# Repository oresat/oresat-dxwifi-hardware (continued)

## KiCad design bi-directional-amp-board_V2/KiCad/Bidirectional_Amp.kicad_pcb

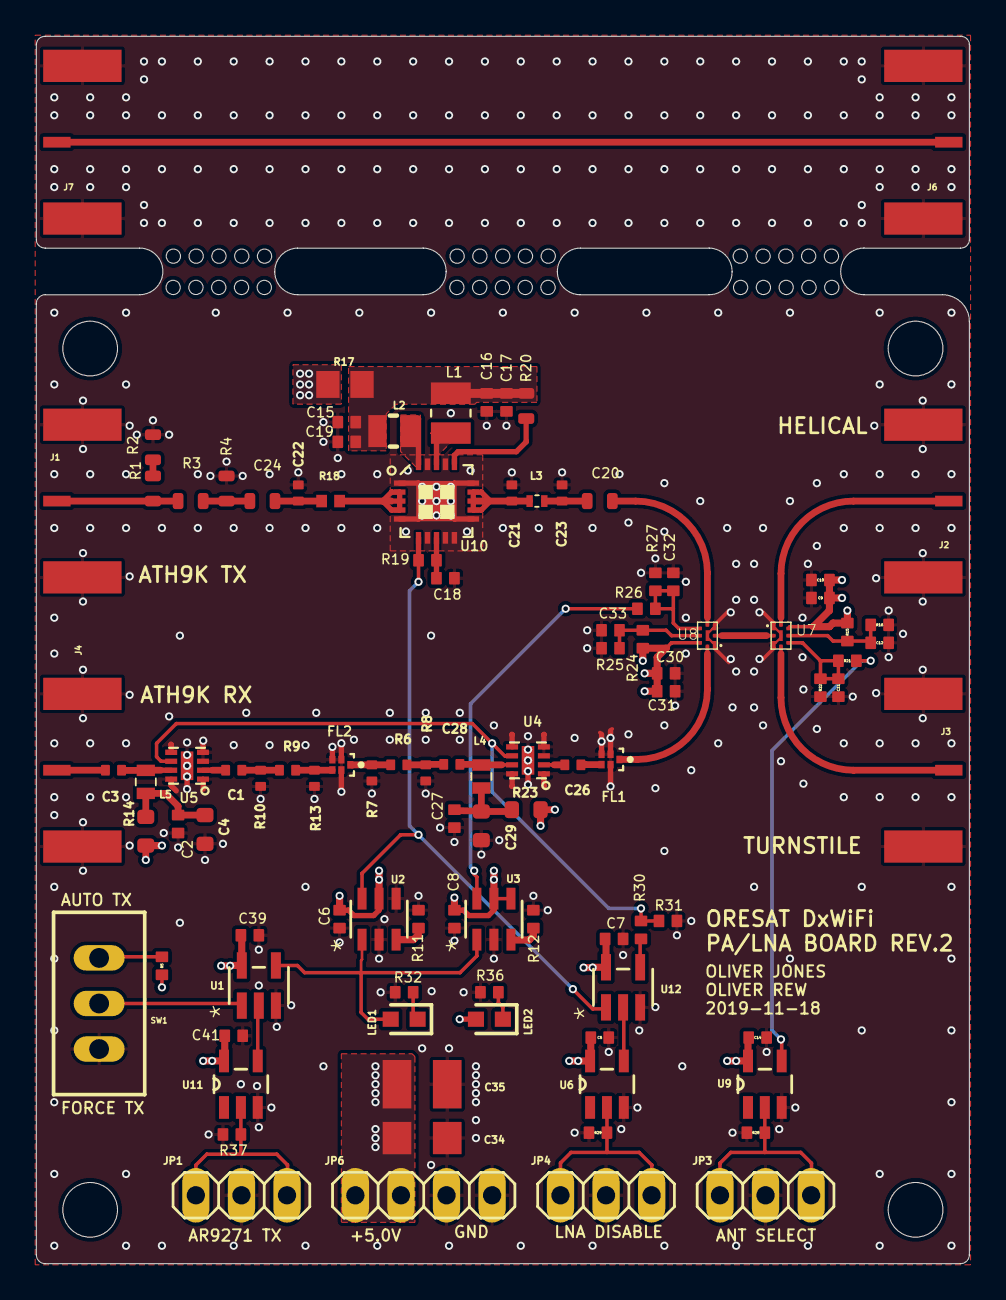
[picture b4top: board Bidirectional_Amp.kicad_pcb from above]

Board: 4 copper layers, 52.0 x 68.4 mm, 135 parts (0 on the bottom side), 53 nets.

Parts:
@HOLE0, @HOLE1, @HOLE2, @HOLE3, @HOLE4, @HOLE5, @HOLE6, @HOLE7, @HOLE8, @HOLE9, @HOLE10, @HOLE11, @HOLE12, @HOLE13, @HOLE14, @HOLE15, @HOLE16, @HOLE17, @HOLE18, @HOLE19, @HOLE20, @HOLE21, @HOLE22, @HOLE23, @HOLE24, @HOLE25, @HOLE26, @HOLE27, @HOLE28, @HOLE29: (no value)
C1, C3, C26, C28: 15p; .0402-C-NOSILK
C2, C27: 15p; .0402-B-NOSILK
C4, C29: 1uF; .0603-B-NOSILK
C5, C6, C7, C8, C10, C14, C31, C39, C41: 100n; .0402-B-NOSILK
C9, C12, C30, C33: 100p; .0402-B-NOSILK
C11, C32: DNP; .0402-B-NOSILK
C15, C16, C17: 100nF; .0402-B-NOSILK
C18: 100pF; .0402-B-NOSILK
C19: 1000pF; .0402-B-NOSILK
C20: 100pF; .0603-C-NOSILK
C21: 3.0pF; .0402-C-NOSILK
C22: 2.2pF; .0402-C-NOSILK
C23: 1.6pF; .0402-C-NOSILK
C24: 4.7pF; .0603-C-NOSILK
C34: 4.7uF; C1206_334
C35: 22uF; C1210_334
FL1, FL2: QPQ1907; FIL_B39162B9417K610
H1, H2, H3, H4: STAND-OFFTIGHT; STAND-OFF-TIGHT
J1, J2, J3, J4, J6, J7: 142-0701-851_ALT; 142-0701-851
JP1, JP3, JP4: 1X03_325
JP6: 1X04_325
L1: 1008HQ-10NXJLB1008_IMPERIAL_2520_METRIC; INDC2520X120N
L2: 6.8nH; 0805CS
L3: 1.2nH; 0402CS1N2XJLW
L4, L5: 68nH; 0603CS-68NXJLW
LED1: LTST-C193KRKT-5A; LEDC1607X80N
LED2: LTST-C193KGKT-5A; LEDC1607X80N
R1, R2: 147; .0603-C-NOSILK
R3: 17.8; .0603-C-NOSILK
R4: 294; .0603-C-NOSILK
R5, R15, R21, R24, R26, R28, R29, R31, R37: 10k; .0402-B-NOSILK
R6, R9: 17.8; .0402-C-NOSILK
R7, R8, R10, R13: 294; .0402-C-NOSILK
R11, R12: 499k; .0402-B-NOSILK
R14, R23: 0; .0603-B-NOSILK
R16, R22, R25, R27: 5.62k; .0402-B-NOSILK
R17: 0; R0805_334
R18: 1.2; R0402_334
R19: 110; .0402-B-NOSILK
R20: 220; .0603-C-NOSILK
R30: 33k; .0402-B-NOSILK
R32, R36: 1k; .0402-B-NOSILK
SW1: TL36PO; TL3XPO_380
U1, U12: SN74LVC1G32DBVR; DBV5
U2, U3: LTC6994-1; TSOT-23_S6
U4, U5: TQP3M9037; DFN8-2X2-WITH-PAD
U6, U9, U11: SN74LV1T34DBVR; SOT95P280X145-5N
U7, U8: QPC1022
U10: TQP9111; QFN50P400X400X102-21N

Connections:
+5V: C5.1, C6.1, C7.1, C8.1, C9.1, C10.1, C14.1, C30.1, C31.1, C34.1, C35.1, C39.1, C41.1, JP6.1, JP6.2, LED2.2, R5.2, R14.2, R15.1, R17.2, R23.2, R24.1, U1.5, U2.5, U3.4, U3.5, U6.5, U7.7, U8.7, U9.5, U11.5, U12.5
ANT_SEL+3.3V: JP3.1, JP3.3, R28.2, U9.2
ANT_SEL_+5.0V: R21.1, U9.4
AR9271_TX_+3.3V: JP1.1, JP1.3, R37.2, U11.2
AS-CTRL: C11.1, R21.2, R22.1, U7.5
AS-EN: C12.1, R15.2, R16.1, U7.6
GND: C2.1, C4.2, C5.2, C6.2, C7.2, C8.2, C9.2, C10.2, C11.2, C12.2, C14.2, C15.2, C16.2, C17.2, C18.2, C19.2, C21.2, C22.2, C23.2, C27.1, C29.2, C30.2, C31.2, C32.2, C33.2, C34.2, C35.2, C39.2, C41.2, FL1.2, FL1.3, FL1.5, FL2.2, FL2.3, FL2.5, J1.GND1, J1.GND2, J1.GND3, J1.GND4, J2.GND1, J2.GND2, J2.GND3, J2.GND4, J3.GND1, J3.GND2, J3.GND3, J3.GND4, J4.GND1, J4.GND2, J4.GND3, J4.GND4, J6.GND1, J6.GND2, J6.GND3, J6.GND4, J7.GND1, J7.GND2, J7.GND3, J7.GND4, JP1.2, JP3.2, JP4.2, JP6.3, JP6.4, R2.1, R4.2, R7.2, R8.2, R10.2, R11.1, R12.1, R13.2, R16.2, R22.2, R25.2, R27.2, R28.1, R29.1, R31.2, R32.1, R36.1, R37.1, SW1.1, U1.3, U2.2, U2.4, U3.2, U4.1, U4.3, U4.4, U4.5, U4.8, U4.PAD, U5.1, U5.3, U5.4, U5.5, U5.8, U5.PAD, U6.3, U7.1, U7.3, U7.9, U8.1, U8.3, U8.9, U9.3, U10.1, U10.5, U10.7, U10.9, U10.10, U10.11, U10.15, U10.17, U10.19, U10.21, U11.3, U12.3
HELICAL: J2.RF1, U7.8
LNA_DISABLE+3.3V: JP4.1, JP4.3, R29.2, U6.2
LNA_DISABLE_+5.0V: U6.4, U12.2
LNA_ON_OFF: R30.1, R31.1, U4.6, U5.6
unnamed: C28.2, R6.1, R8.1
unnamed: J1.RF1, R1.2, R3.1
unnamed: R5.1, SW1.3
unnamed: R1.1, R2.2
unnamed: SW1.2, U1.1
unnamed: FL2.4, R9.1, R13.1
unnamed: C1.2, U5.2
unnamed: C3.1, L5.1, U5.7
unnamed: C2.2, C4.1, L5.2, R14.1
unnamed: LED1.2, U1.4, U2.1, U3.1
unnamed: R11.2, U2.3
unnamed: C3.2, J4.RF1
unnamed: U1.2, U11.4
unnamed: R12.2, U3.3
unnamed: LED1.1, R32.2
unnamed: L1.1, U10.18
unnamed: R30.2, U12.4
unnamed: C15.1, C16.1, C17.1, C19.1, L1.2, L2.2, R17.1, R20.2
unnamed: C18.1, R19.2, U10.8
unnamed: C21.1, L3.1, U10.12, U10.13, U10.14
unnamed: C22.1, C24.2, R18.1
unnamed: C26.2, U4.2
unnamed: C20.1, C23.1, L3.2
unnamed: C28.1, L4.1, U4.7
unnamed: C27.2, C29.1, L4.2, R23.1
unnamed: R20.1, U10.16
unnamed: L2.1, U10.20
unnamed: C26.1, FL1.4
unnamed: LED2.1, R36.2
unnamed: R18.2, U10.2, U10.3, U10.4
PA_MATCH_OUT: C20.2, U8.4
PA_ON_LNA_OFF: R19.1, U2.6, U10.6, U12.1
PA_PAD_OUT: C24.1, R3.2, R4.1
PA_PAD_OUT1: FL2.1, R6.2, R7.1
PA_PAD_OUT2: C1.1, R9.2, R10.1
RX_IN: FL1.1, U8.8
THROUGH: J6.RF1, J7.RF1
TURNSTILE: J3.RF1, U7.4
TXRX-CTRL: C32.1, R26.2, R27.1, U8.5
TXRX-EN: C33.1, R24.2, R25.1, U8.6
TX_RX_COMMON: U7.2, U8.2
TX_RX_CTL: R26.1, U3.6

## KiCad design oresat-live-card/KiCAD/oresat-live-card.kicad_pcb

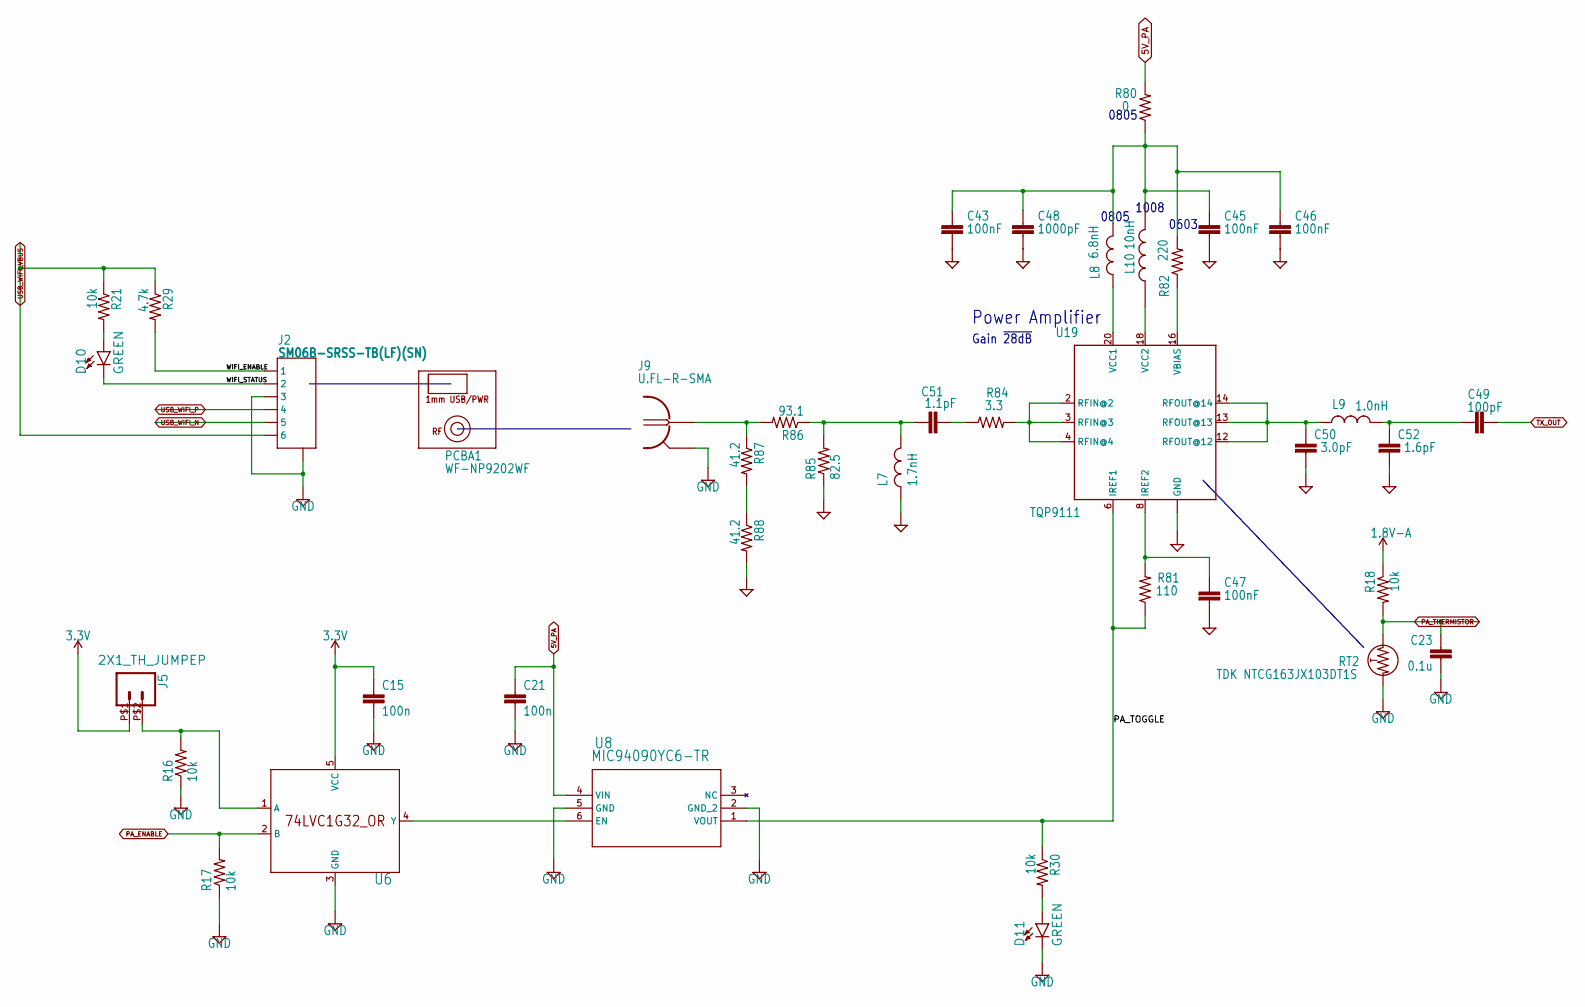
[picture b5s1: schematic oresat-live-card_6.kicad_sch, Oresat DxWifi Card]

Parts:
C15, C21: 100n; .0603-A
C23: 0.1u; .0603-A
C43, C45, C46: CGA2B1X7R1C104K050BC; .0402-B-NOSILK
C47: CGA2B1X7R1C104K050BC; .0402-C-NOSILK
C48: CGA2B2NP01H102J050BA; .0402-B-NOSILK
C49: GCM1885C1H101JA16D; .0402-C-NOSILK
C50: 04025U3R0BAT2A; .0402-C-NOSILK
C51: 04025J1R1PBSTR\500; .0402-C-NOSILK
C52: 04025U1R6BAT2A; .0402-C-NOSILK
D10, D11: 150060VS55040; LED-0603
J2: SM06B-SRSS-TB(LF)(SN); CONN_SM06B-SRSS-TB_JST
J5: 2X1_TH_JUMPEP; 2X1
J9: U.FL-R-SMA; U.FL-R-SMT
L7: 0402DC-1N7XJRU; .0402-C-NOSILK
L8: 0805CS-060XJLC; .0805-C-NOSILK
L9: MLK1005S1N0ST000; .0402-C-NOSILK
L10: Fixed Inductors 1008 10nH Unshld 5% 1.6A 60mOhms; INDC2928X203N
PCBA1: WF-NP9202WF; WF-NP9202
R16, R17, R18, R21, R30: 10k; .0603-A
R29: 4.7k; .0603-A
R80: ERJ-6GEY0R00V; R0805
R81: ERJ-2RKF1100X; .0402-B-NOSILK
R82: ERJ-3EKF2200V; .0603-C-NOSILK
R84: CRCW04023R30FKED; .0402-C-NOSILK
R85: ERJ-3EKF82R5V; .0603-A
R86: ERJ-3EKF93R1V; .0603-A
R87, R88: ERJ-3EKF41R2V; .0603-A
RT2: TDK NTCG163JX103DT1S; 0603-THERMISTOR-B
U6: SN74LVC1G32QDBVRQ1; DBV5
U8: MIC94090YC6-TR; SC-70-6_MCH
U19: TQP9111; QFN50P400X400X102-21N

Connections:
1.8V-A: R18.1; also elsewhere on the board
3.3V: C15.1, J5.P$1 (1), U6.5 (VCC); also elsewhere on the board
5V_PA: C21.1, R80.2, U8.4 (VIN); also elsewhere on the board
/oresat-live-card_6/PA_TOGGLE: R30.1, R81.1, U8.1 (VOUT), U19.6 (IREF1)
/oresat-live-card_6/WIFI_ENABLE: J2.1, R29.2
/oresat-live-card_6/WIFI_STATUS: D10.C, J2.2
unnamed: C43.1, C45.1, C46.1, C48.1, L8.2, L10.2, R80.1, R82.2
unnamed: C47.1, R81.2, U19.8 (IREF2)
unnamed: C49.1, C52.1, L9.2
unnamed: C50.1, L9.1, U19.12 (RFOUT@12), U19.13 (RFOUT@13), U19.14 (RFOUT@14)
unnamed: C51.1, L7.2, R85.2, R86.1
unnamed: C51.2, R84.1
unnamed: D10.A, R21.2
unnamed: D11.A, R30.2
unnamed: J5.P$2 (2), R16.2, U6.1 (A)
unnamed: J9.1, R86.2, R87.1
unnamed: L8.1, U19.20 (VCC1)
unnamed: L10.1, U19.18 (VCC2)
unnamed: R82.1, U19.16 (VBIAS)
unnamed: R84.2, U19.2 (RFIN@2), U19.3 (RFIN@3), U19.4 (RFIN@4)
unnamed: R87.2, R88.1
unnamed: U6.4 (Y), U8.6 (EN)
PA_ENABLE: R17.2, U6.2 (B); also elsewhere on the board
PA_THERMISTOR: C23.1, R18.2, RT2.1; also elsewhere on the board
TX_OUT: C49.2; also elsewhere on the board
USB_WIFI_N: J2.5; also elsewhere on the board
USB_WIFI_P: J2.4; also elsewhere on the board
USB_WIFI_VBUS: J2.6, R21.1, R29.1; also elsewhere on the board

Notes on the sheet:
1008
0805
Gain ~{28dB}
0603
Power Amplifier

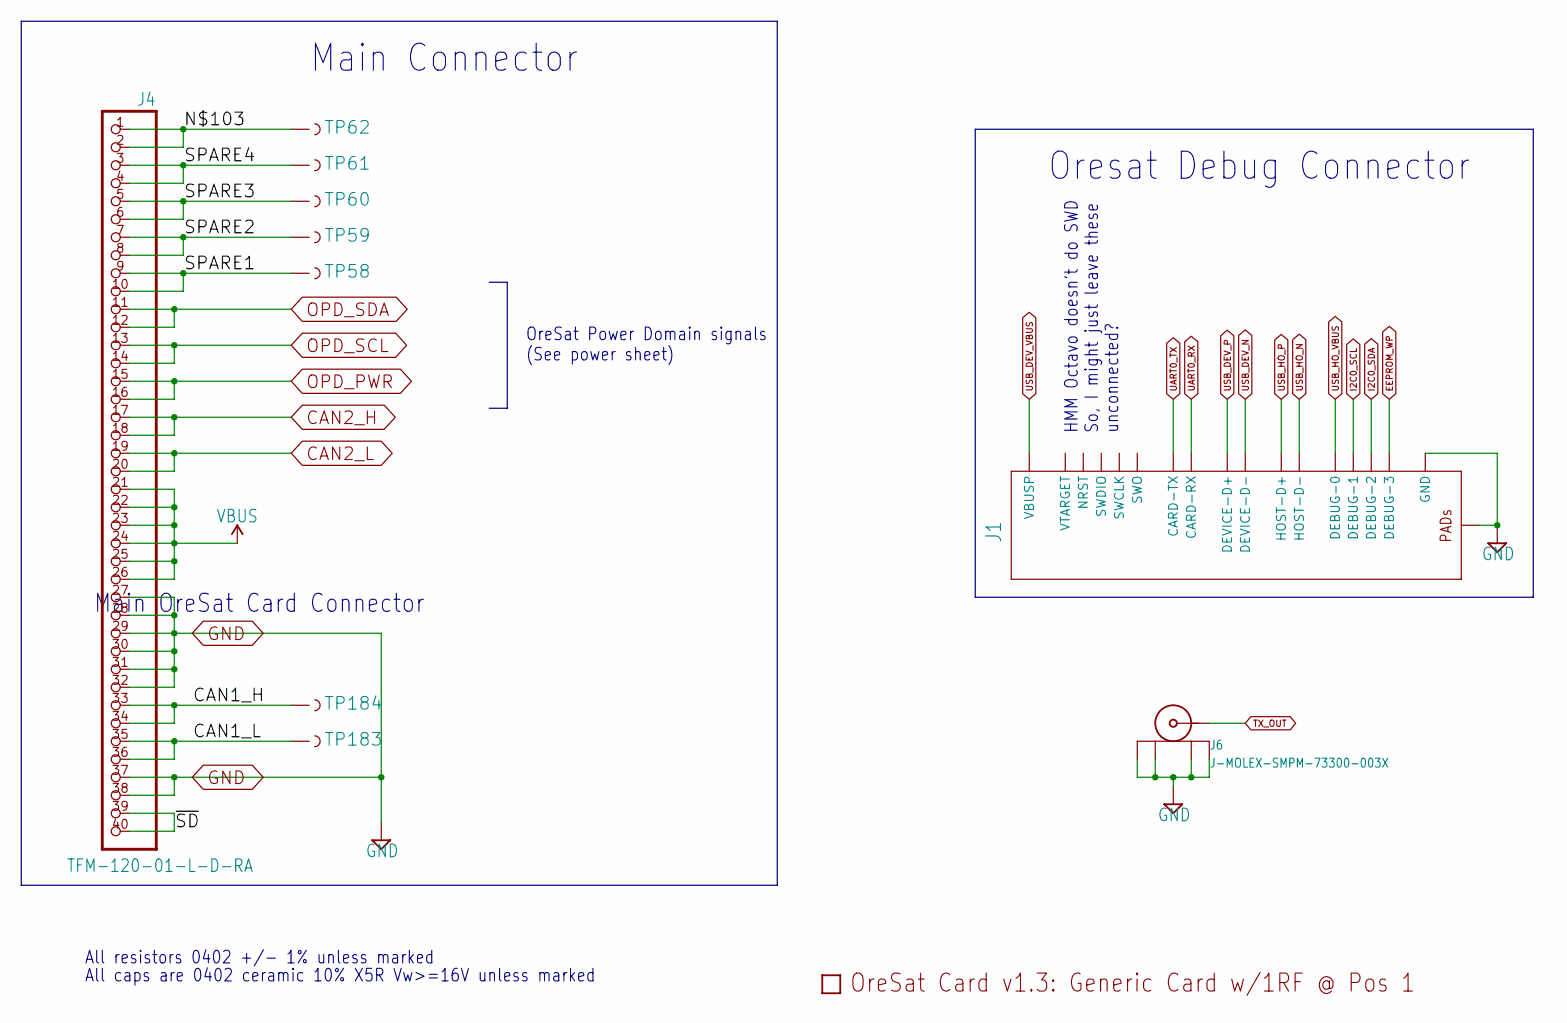
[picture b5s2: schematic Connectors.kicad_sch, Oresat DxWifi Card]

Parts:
J1: ORESAT-DEBUG-CONNECTOR-CARD; TE_2-1734592-0
J4: TFM-120-01-L-D-RA; J-SAMTEC-TFM-120-X1-XXX-D-RA
J6: J-MOLEX-SMPM-73300-003X; J-MOLEX-SMPM-073300-003X
PCB1: ORESAT-CARD-V1.3-GENERIC-1RF-POS1
TP58, TP59, TP60, TP61, TP62, TP183, TP184: TEST-POINT3X4; PAD.03X.04

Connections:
/Connectors/CAN1_H: J4.33, J4.34, TP184.1
/Connectors/CAN1_L: J4.35, J4.36, TP183.1
/Connectors/N$103: J4.1, J4.2, TP62.1
/Connectors/SPARE1: J4.9, J4.10, TP58.1
/Connectors/SPARE2: J4.7, J4.8, TP59.1
/Connectors/SPARE3: J4.5, J4.6, TP60.1
/Connectors/SPARE4: J4.3, J4.4, TP61.1
/Connectors/~SD: J4.39, J4.40
CAN2_H: J4.17, J4.18; also elsewhere on the board
CAN2_L: J4.19, J4.20; also elsewhere on the board
EEPROM_WP: J1.20 (DEBUG-3); also elsewhere on the board
I2C0_SCL: J1.18 (DEBUG-1); also elsewhere on the board
I2C0_SDA: J1.19 (DEBUG-2); also elsewhere on the board
OPD_PWR: J4.15, J4.16; also elsewhere on the board
OPD_SCL: J4.13, J4.14; also elsewhere on the board
OPD_SDA: J4.11, J4.12; also elsewhere on the board
TX_OUT: J6.RF (CENTER); also elsewhere on the board
UART0_RX: J1.12 (CARD-RX); also elsewhere on the board
UART0_TX: J1.13 (CARD-TX); also elsewhere on the board
USB_DEV_N: J1.5 (DEVICE-D-); also elsewhere on the board
USB_DEV_P: J1.4 (DEVICE-D+); also elsewhere on the board
USB_DEV_VBUS: J1.1 (VBUSP), J1.2 (VBUSP); also elsewhere on the board
USB_HO_N: J1.8 (HOST-D-); also elsewhere on the board
USB_HO_P: J1.7 (HOST-D+); also elsewhere on the board
USB_HO_VBUS: J1.17 (DEBUG-0); also elsewhere on the board
VBUS: J4.21, J4.22, J4.23, J4.24, J4.25, J4.26; also elsewhere on the board

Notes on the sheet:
OreSat Power Domain signals (See power sheet)
All resistors 0402 +/- 1% unless marked
Main Connector
Main OreSat Card Connector
All caps are 0402 ceramic 10% X5R Vw>=16V unless marked
HMM Octavo doesn't do SWD So, I might just leave these unconnected?
Oresat Debug Connector

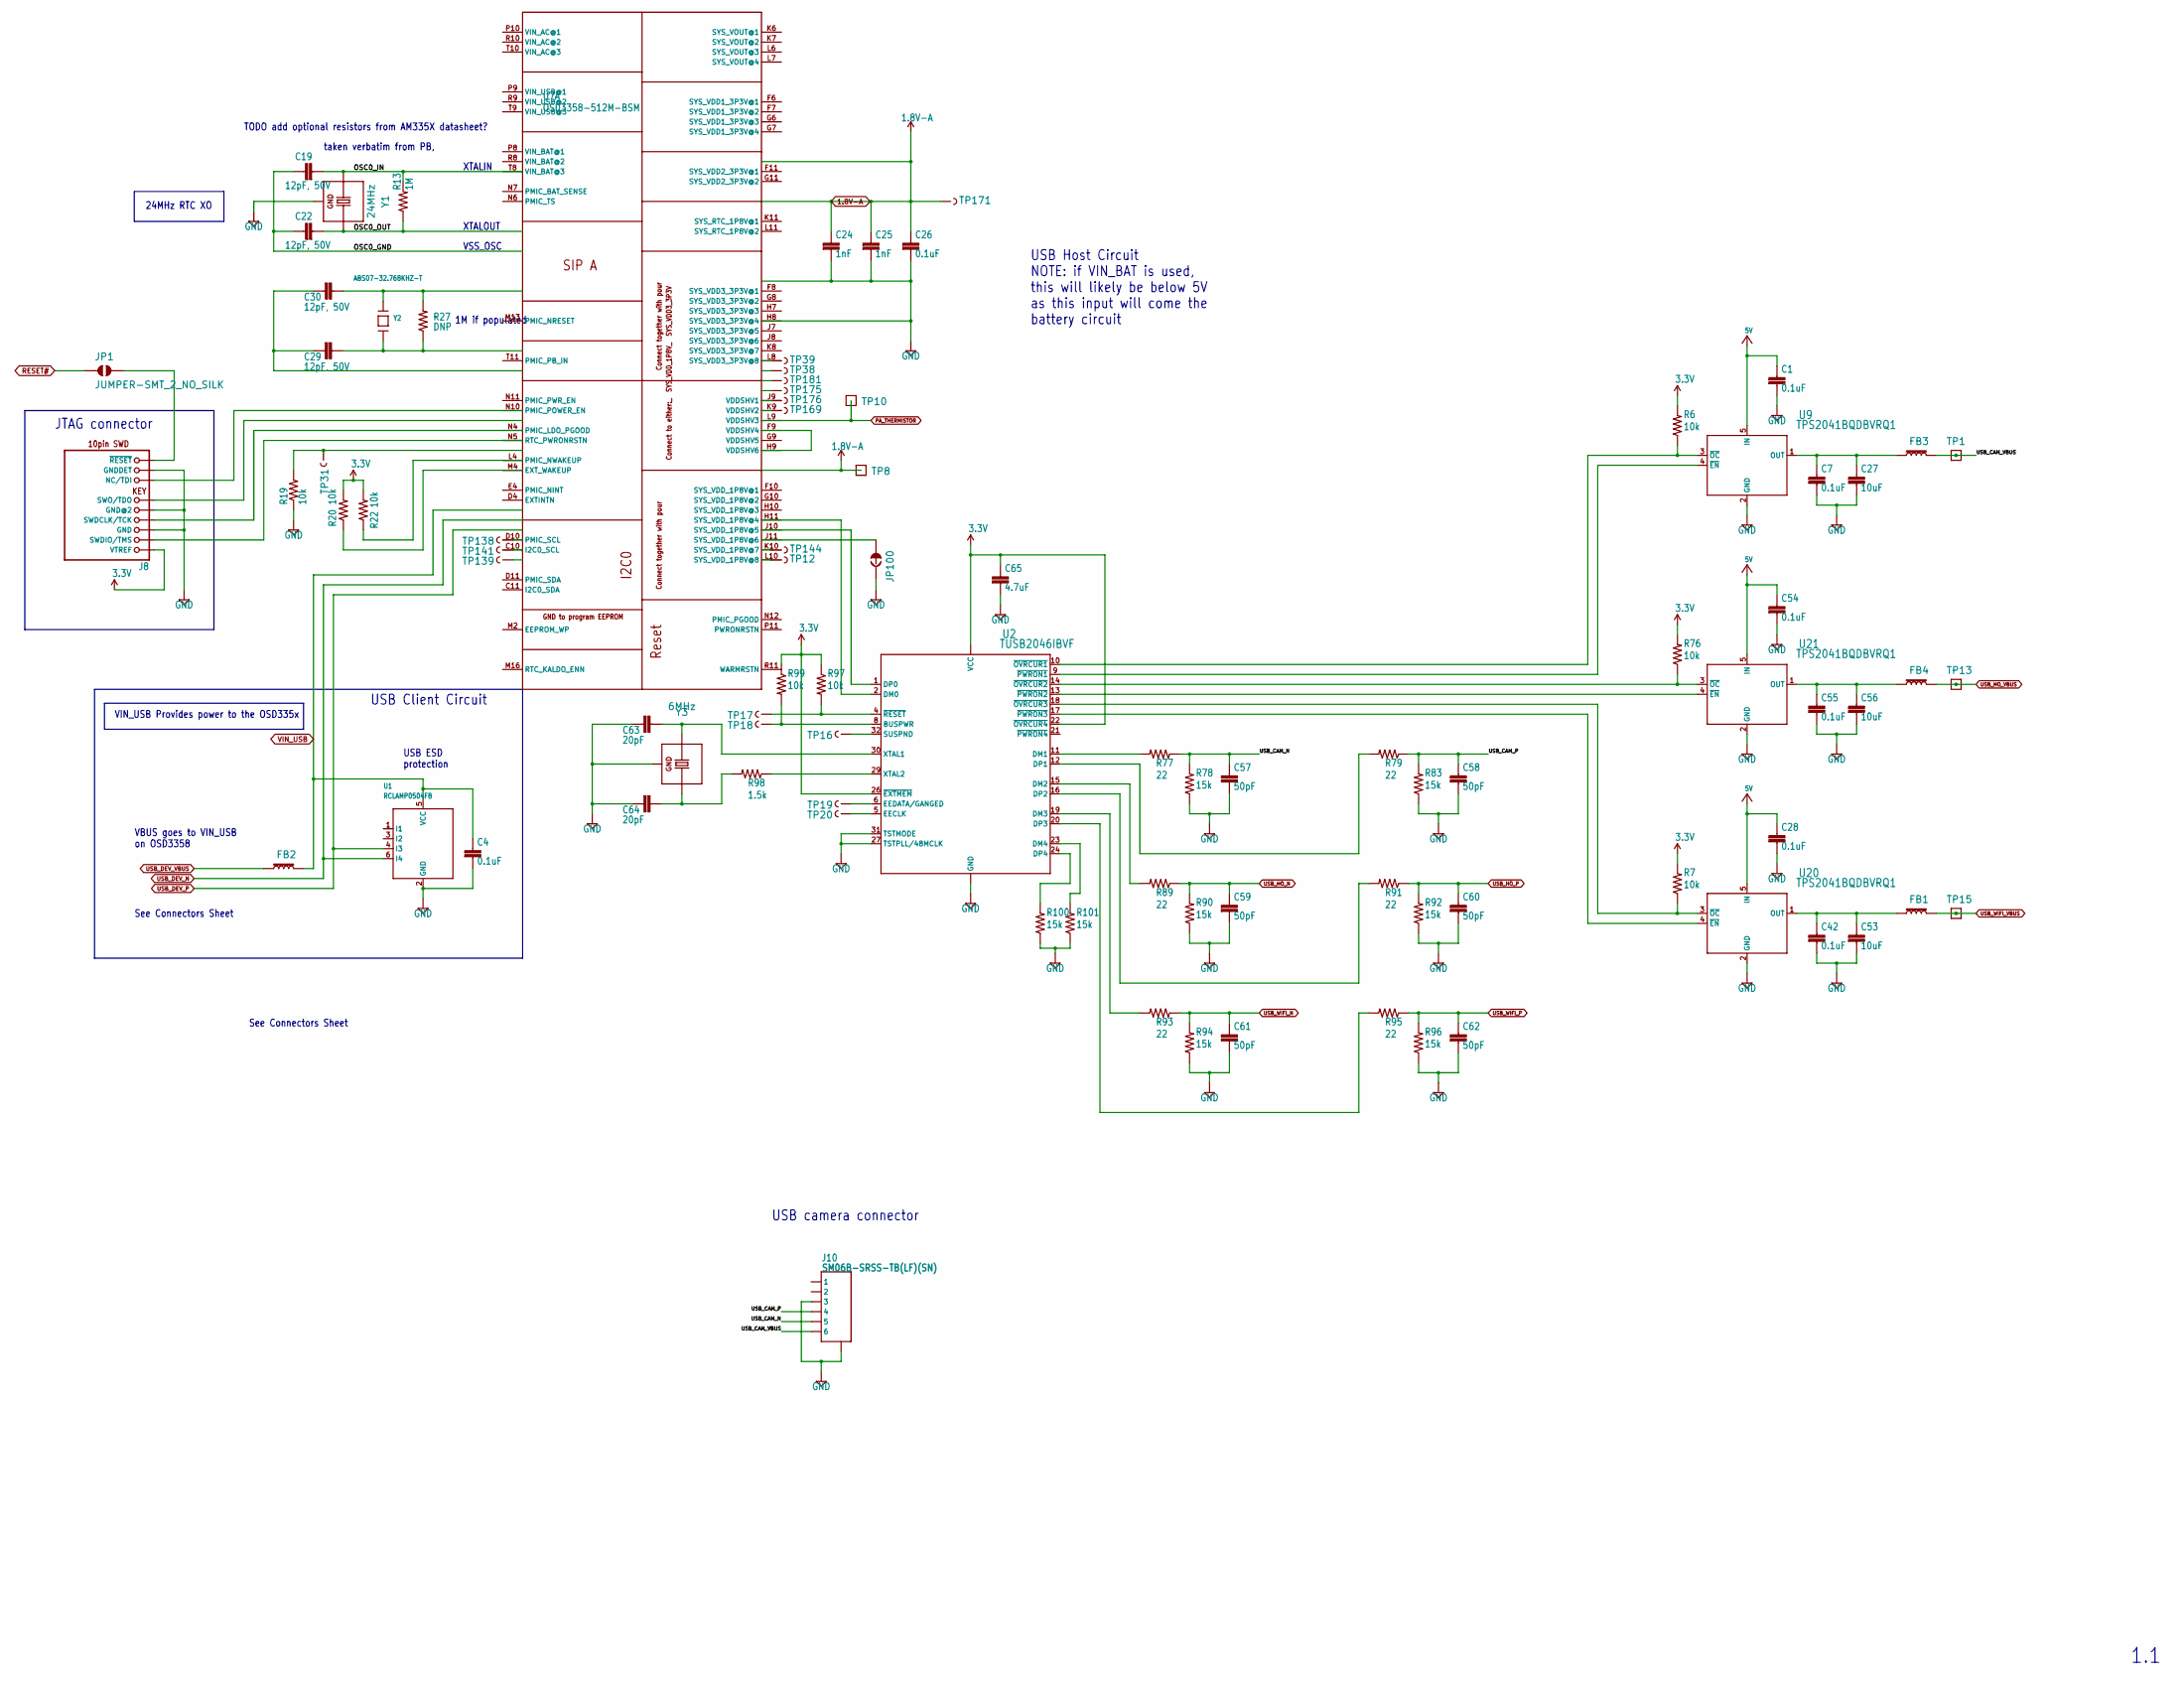
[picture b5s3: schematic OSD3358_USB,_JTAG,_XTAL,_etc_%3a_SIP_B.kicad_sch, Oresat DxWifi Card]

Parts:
C1, C4, C7, C28, C42, C54, C55: 0.1uF; .0603-A
C19, C22, C29, C30: 12pF, 50V; .0603-A
C24, C25: 1nF; .0805-B
C26: 0.1uF; .0805-B
C27, C53, C56: 10uF; .0603-A
C57, C58, C59, C60, C61, C62: 50pF; .0603-A
C63, C64: 20pF; .0603-A
C65: 4.7uF; .0603-A
FB1, FB2, FB3, FB4: BLM18KG300JH1D; 0603
J8: FTSH-105-XX-X-DV-K; CON10_2X5_DUK_FTSH
J10: SM06B-SRSS-TB(LF)(SN); CONN_SM06B-SRSS-TB_JST
JP1: JUMPER-SMT_2_NO_SILK; SMT-JUMPER_2_NO_SILK
JP100: JUMPER-SMT_2_NC_TRACE_SILK; SMT-JUMPER_2_NC_TRACE_SILK
R6, R7, R19, R20, R22, R76, R97, R99: 10k; .0603-A
R13: 1M; .0603-A
R27: DNP; .0603-A
R77, R79, R89, R91, R93, R95: 22; .0603-A
R78, R83, R90, R92, R94, R96, R100, R101: 15k; .0603-A
R98: 1.5k; .0603-A
TP1, TP8, TP10, TP13, TP15: TEST-POINT; 2MM-TEST-POINT
TP12, TP16, TP17, TP18, TP19, TP20, TP31, TP38, TP39, TP138, TP139, TP141, TP144, TP169, TP171, TP175, TP176, TP181: TEST-POINT3X4; PAD.03X.04
U1: RCLAMP0504FB; SC70-6
U2: TUSB2046IBVF; QFP80P900X900X160-32N
U7: OSD3358-512M-BSM; OSD335X-BGA-256
U9, U20, U21: TPS2041BQDBVRQ1; DBV5
Y1: 24MHz; 5X3.2-4SMD
Y2: ABS07-32.768KHZ-T; CRYSTAL_3.2X1.5
Y3: 6MHz; ECS_ECS-060-18-20BM-JEN-TR

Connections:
1.8V-A: C24.1, C25.1, C26.1, TP8.1, TP171.1, U7.A7 (SYS_ADC_1P8V), U7.B7 (VREFP), U7.N13 (PMIC_MUX_IN); also elsewhere on the board
3.3V: C65.1, J8.1 (VTREF), R6.2, R7.2, R20.2, R22.2, R76.2, R97.1, R99.1, U2.3 (VCC), U2.22 (~OVRCUR4), U2.25 (VCC), U2.26 (~EXTMEM), U7.F6 (SYS_VDD1_3P3V@1), U7.F7 (SYS_VDD1_3P3V@2), U7.G6 (SYS_VDD1_3P3V@3), U7.G7 (SYS_VDD1_3P3V@4); also elsewhere on the board
5V: C1.1, C28.1, C54.1, U7.P10 (VIN_AC@1), U7.R10 (VIN_AC@2), U7.T10 (VIN_AC@3), U9.5 (IN), U20.5 (IN), U21.5 (IN); also elsewhere on the board
/OSD3358 PWR, ETC. : SIP A, E, F/N$53: U7.K11 (SYS_RTC_1P8V@1), U7.L11 (SYS_RTC_1P8V@2); also elsewhere on the board
/OSD3358 PWR, ETC. : SIP A, E, F/PMIC_PGOOD: U7.N12 (PMIC_PGOOD), U7.P11 (PWRONRSTN); also elsewhere on the board
/OSD3358 USB, JTAG, XTAL, etc : SIP B/OSC0_GND: C19.1, C22.1, U7.N15 (OSC0_GND)
/OSD3358 USB, JTAG, XTAL, etc : SIP B/OSC0_IN: C19.2, R13.2, U7.P16 (OSC0_IN), Y1.1 (X1)
/OSD3358 USB, JTAG, XTAL, etc : SIP B/OSC0_OUT: C22.2, R13.1, U7.N16 (OSC0_OUT), Y1.3 (X2)
/OSD3358 USB, JTAG, XTAL, etc : SIP B/USB_CAM_N: C57.1, J10.5, R77.1, R78.2
/OSD3358 USB, JTAG, XTAL, etc : SIP B/USB_CAM_P: C58.1, J10.4, R79.1, R83.2
/OSD3358 USB, JTAG, XTAL, etc : SIP B/USB_CAM_VBUS: FB3.2, J10.6, TP1.1
unnamed: C7.1, C27.1, FB3.1, U9.1 (OUT)
unnamed: C29.1, R27.1, U7.A5 (OSC1_OUT), Y2.P$1
unnamed: C29.2, C30.2, U7.B5 (OSC1_GND)
unnamed: C30.1, R27.2, U7.A6 (OSC1_IN), Y2.P$2
unnamed: C42.1, C53.1, FB1.1, U20.1 (OUT)
unnamed: C55.1, C56.1, FB4.1, U21.1 (OUT)
unnamed: C63.1, U2.30 (XTAL1), Y3.3 (X1)
unnamed: C64.1, R98.2, Y3.1 (X2)
unnamed 70: U7.C16 (MMC0_DAT2); also elsewhere on the board
unnamed 71: U7.C15 (MMC0_DAT3); also elsewhere on the board
unnamed 72: U7.B16 (MMC0_CMD); also elsewhere on the board
unnamed 73: U7.B15 (MMC0_CLK); also elsewhere on the board
unnamed 74: U7.A16 (MMC0_DAT0); also elsewhere on the board
unnamed 75: U7.A15 (MMC0_DAT1); also elsewhere on the board
unnamed 76: U7.C14 (SPI0_CS1); also elsewhere on the board
unnamed: J8.2 (SWDIO/TMS), U7.D2 (TMS)
unnamed: J8.4 (SWDCLK/TCK), U7.D1 (TCK)
unnamed: J8.6 (SWO/TDO), U7.C2 (TDO)
unnamed: J8.8 (NC/TDI), U7.C1 (TDI)
unnamed: J8.10 (~RESET), JP1.2
unnamed: JP100.1, U7.L14 (USB1_ID)
unnamed 87: U7.G3 (LCD_DATA0); also elsewhere on the board
unnamed 90: U7.G2 (LCD_DATA1); also elsewhere on the board
unnamed 93: U7.G1 (LCD_DATA2); also elsewhere on the board
unnamed 96: U7.H3 (LCD_DATA3); also elsewhere on the board
unnamed 99: U7.H2 (LCD_DATA4); also elsewhere on the board
unnamed 108: U7.P13 (GPMC_A5); also elsewhere on the board
unnamed 109: U7.T14 (GPMC_A6); also elsewhere on the board
unnamed 110: U7.R14 (GPMC_A7); also elsewhere on the board
unnamed 111: U7.P14 (GPMC_A8); also elsewhere on the board
unnamed: R6.1, U2.10 (~OVRCUR1), U9.3 (~OC)
unnamed: R7.1, U2.18 (~OVRCUR3), U20.3 (~OC)
unnamed 114: U7.R3 (GPMC_AD0); also elsewhere on the board
unnamed 115: U7.T2 (GPMC_AD4); also elsewhere on the board
unnamed 116: U7.P1 (GPMC_CSN2); also elsewhere on the board
unnamed 117: U7.P2 (GPMC_CSN1); also elsewhere on the board
unnamed 118: U7.T1 (GPMC_AD5); also elsewhere on the board
unnamed 119: U7.T3 (GPMC_AD3); also elsewhere on the board
unnamed 120: U7.R13 (GPMC_A4); also elsewhere on the board
unnamed 121: U7.P4 (GPMC_AD6); also elsewhere on the board
unnamed 122: U7.R1 (GPMC_AD2); also elsewhere on the board
unnamed 123: U7.R2 (GPMC_AD1); also elsewhere on the board
unnamed 124: U7.R4 (GPMC_AD7); also elsewhere on the board
unnamed 126: U7.M16 (RTC_KALDO_ENN); also elsewhere on the board
unnamed: R19.2, TP31.1, U7.D3 (TRSTN)
unnamed: R20.1, U7.E3 (EMU1)
unnamed: R22.1, U7.E2 (EMU0)
unnamed 130: U7.L1 (LCD_DATA14); also elsewhere on the board
unnamed 131: U7.H1 (LCD_DATA5); also elsewhere on the board
unnamed 132: U7.J3 (LCD_DATA6); also elsewhere on the board
unnamed 133: U7.M3 (LCD_DATA15); also elsewhere on the board
unnamed 134: U7.L3 (LCD_DATA12); also elsewhere on the board
unnamed 135: U7.K2 (LCD_DATA10); also elsewhere on the board
unnamed 136: U7.J1 (LCD_DATA8); also elsewhere on the board
unnamed 137: U7.J2 (LCD_DATA7); also elsewhere on the board
unnamed 138: U7.K3 (LCD_DATA9); also elsewhere on the board
unnamed 139: U7.K1 (LCD_DATA11); also elsewhere on the board
unnamed 140: U7.L2 (LCD_DATA13); also elsewhere on the board
unnamed 152: U7.C10 (I2C0_SCL), U7.D10 (PMIC_SCL); also elsewhere on the board
unnamed 153: U7.C11 (I2C0_SDA), U7.D11 (PMIC_SDA); also elsewhere on the board
unnamed 154: U7.M2 (EEPROM_WP); also elsewhere on the board
unnamed: R76.1, U2.14 (~OVRCUR2), U21.3 (~OC)
unnamed: R77.2, U2.11 (DM1)
unnamed: R79.2, U2.12 (DP1)
unnamed: R89.2, U2.15 (DM2)
unnamed: R91.2, U2.16 (DP2)
unnamed: R93.2, U2.19 (DM3)
unnamed: R95.2, U2.20 (DP3)
unnamed: R97.2, TP17.1, U2.4 (~RESET)
unnamed: R98.1, U2.29 (XTAL2)
unnamed: R99.2, TP18.1, U2.8 (BUSPWR)
unnamed: R100.2, U2.24 (DP4)
unnamed: R101.2, U2.23 (DM4)
unnamed 171: U7.F10 (SYS_VDD_1P8V@1), U7.G10 (SYS_VDD_1P8V@2), U7.H10 (SYS_VDD_1P8V@3), U7.H11 (SYS_VDD_1P8V@4), U7.J10 (SYS_VDD_1P8V@5), U7.J11 (SYS_VDD_1P8V@6), U7.K10 (SYS_VDD_1P8V@7), U7.L10 (SYS_VDD_1P8V@8); also elsewhere on the board
unnamed: TP12.1, U7.M14 (USB1_DRVVBUS)
unnamed: TP16.1, U2.32 (SUSPND)
unnamed: TP19.1, U2.6 (EEDATA/GANGED)
unnamed: TP20.1, U2.5 (EECLK)
unnamed 176: U7.A4 (XDMA_EVENT_INTR0); also elsewhere on the board
unnamed: TP38.1, U7.B8 (AIN1)
unnamed: TP39.1, U7.A8 (AIN0)
unnamed 185: U7.T12 (GPMC_A0); also elsewhere on the board
unnamed 186: U7.T13 (GPMC_A3); also elsewhere on the board
unnamed 187: U7.T16 (GPMC_A11); also elsewhere on the board
unnamed 188: U7.T4 (GPMC_AD8); also elsewhere on the board
unnamed 189: U7.T5 (GPMC_AD11); also elsewhere on the board
unnamed 190: U7.T7 (GPMC_CLK); also elsewhere on the board
unnamed 191: U7.R7 (GPMC_CSN3); also elsewhere on the board
unnamed 192: U7.T15 (GPMC_A9); also elsewhere on the board
unnamed 193: U7.R16 (GPMC_WPN); also elsewhere on the board
unnamed 194: U7.P15 (GPMC_WAIT0); also elsewhere on the board
unnamed 195: U7.R5 (GPMC_AD10); also elsewhere on the board
unnamed 196: U7.R15 (GPMC_A10); also elsewhere on the board
unnamed 197: U7.R12 (GPMC_A1); also elsewhere on the board
unnamed 198: U7.R6 (GPMC_AD13); also elsewhere on the board
unnamed 199: U7.P3 (GPMC_CSN0); also elsewhere on the board
unnamed 200: U7.P5 (GPMC_AD9); also elsewhere on the board
unnamed 201: U7.P6 (GPMC_AD12); also elsewhere on the board
unnamed 202: U7.N14 (GPMC_BEN1); also elsewhere on the board
unnamed 203: U7.P12 (GPMC_A2); also elsewhere on the board
unnamed 204: U7.N2 (GPMC_WEN); also elsewhere on the board
unnamed 205: U7.N1 (GPMC_OEN_REN); also elsewhere on the board
unnamed 206: U7.N6 (PMIC_TS); also elsewhere on the board
unnamed 207: U7.N7 (PMIC_BAT_SENSE), U7.P8 (VIN_BAT@1), U7.R8 (VIN_BAT@2), U7.T8 (VIN_BAT@3); also elsewhere on the board
unnamed 208: U7.N3 (GPMC_BEN0_CLE); also elsewhere on the board
unnamed 209: U7.M1 (GPMC_ADVN_ALE); also elsewhere on the board
unnamed 210: U7.G16 (MII1_TXD2); also elsewhere on the board
unnamed 211: U7.H15 (MII1_TXD0); also elsewhere on the board
unnamed: TP138.1, U7.K14 (USB0_ID)
unnamed: TP139.1, U7.J15 (USB0_DRVVBUS)
unnamed: TP141.1, U7.K13 (USB0_CE)
unnamed 215: U7.J14 (RMII1_REF_CLK); also elsewhere on the board
unnamed: TP144.1, U7.L13 (USB1_CE)
unnamed 217: U7.K4 (NC@3); also elsewhere on the board
unnamed 218: U7.G14 (MII1_TX_EN); also elsewhere on the board
unnamed 219: U7.H14 (MII1_TXD1); also elsewhere on the board
unnamed 220: U7.J6 (NC@2); also elsewhere on the board
unnamed 221: U7.F2 (LCD_HSYNC); also elsewhere on the board
unnamed 222: U7.F3 (LCD_VSYNC); also elsewhere on the board
unnamed 223: U7.G4 (VDD_CORE); also elsewhere on the board
unnamed 224: U7.F4 (VDDS_DDR); also elsewhere on the board
unnamed 225: U7.H6 (VPP); also elsewhere on the board
unnamed 226: U7.E13 (MDIO); also elsewhere on the board
unnamed 227: U7.E1 (LCD_AC_BIAS_EN); also elsewhere on the board
unnamed 228: U7.F13 (VDD_MPU); also elsewhere on the board
unnamed 229: U7.F11 (SYS_VDD2_3P3V@1), U7.G11 (SYS_VDD2_3P3V@2); also elsewhere on the board
unnamed 230: U7.F1 (LCD_PCLK); also elsewhere on the board
unnamed 231: U7.G13 (VDDS_PLL); also elsewhere on the board
unnamed 232: U7.D4 (EXTINTN), U7.E4 (PMIC_NINT); also elsewhere on the board
unnamed: TP169.1, U7.C8 (AIN5)
unnamed 234: U7.D12 (NC@1); also elsewhere on the board
unnamed 235: U7.D5 (CAP_VDD_RTC); also elsewhere on the board
unnamed 236: U7.D13 (MDC); also elsewhere on the board
unnamed: TP175.1, U7.C6 (AIN3)
unnamed: TP176.1, U7.C7 (AIN4)
unnamed 239: U7.C12 (UART0_CTSN); also elsewhere on the board
unnamed 240: U7.C13 (UART0_RTSN); also elsewhere on the board
unnamed 241: U7.C5 (ECAP0_IN_PWM0_OUT); also elsewhere on the board
unnamed: TP181.1, U7.B6 (AIN2)
unnamed: U2.1 (DP0), U7.L15 (USB1_DP)
unnamed: U2.2 (DM0), U7.L16 (USB1_DM)
unnamed: U2.9 (~PWRON1), U9.4 (~EN)
unnamed: U2.13 (~PWRON2), U21.4 (~EN)
unnamed: U2.17 (~PWRON3), U20.4 (~EN)
unnamed: U7.D6 (PMIC_MUX_OUT), U7.D7 (AIN7)
unnamed 250: U7.A11 (UART1_RXD); also elsewhere on the board
unnamed 251: U7.B11 (UART1_TXD); also elsewhere on the board
unnamed 252: U7.A14 (SPI0_CS0); also elsewhere on the board
unnamed 253: U7.B13 (SPI0_D0); also elsewhere on the board
unnamed 254: U7.B14 (SPI0_D1); also elsewhere on the board
unnamed 255: U7.A13 (SPI0_SCLK); also elsewhere on the board
PA_ENABLE: U7.H16 (MII1_TX_CLK); also elsewhere on the board
PA_THERMISTOR: TP10.1, U7.C9 (AIN6); also elsewhere on the board
RESET#: JP1.1, U7.R11 (WARMRSTN); also elsewhere on the board
UART0_RX: U7.A12 (UART0_RXD); also elsewhere on the board
UART0_TX: U7.B12 (UART0_TXD); also elsewhere on the board
USB_DEV_N: U1.6 (I4), U7.K16 (USB0_DM); also elsewhere on the board
USB_DEV_P: U1.4 (I3), U7.K15 (USB0_DP); also elsewhere on the board
USB_DEV_VBUS: FB2.1; also elsewhere on the board
USB_HO_N: C59.1, R89.1, R90.2; also elsewhere on the board
USB_HO_P: C60.1, R91.1, R92.2; also elsewhere on the board
USB_HO_VBUS: FB4.2, TP13.1; also elsewhere on the board
USB_WIFI_N: C61.1, R93.1, R94.2; also elsewhere on the board
USB_WIFI_P: C62.1, R95.1, R96.2; also elsewhere on the board
USB_WIFI_VBUS: FB1.2, TP15.1; also elsewhere on the board
VDD: U7.K6 (SYS_VOUT@1), U7.K7 (SYS_VOUT@2), U7.L6 (SYS_VOUT@3), U7.L7 (SYS_VOUT@4); also elsewhere on the board
VIN_USB: C4.1, FB2.2, U1.5 (VCC), U7.J16 (USB0_VBUS), U7.P9 (VIN_USB@1), U7.R9 (VIN_USB@2), U7.T9 (VIN_USB@3); also elsewhere on the board

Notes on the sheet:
XTALOUT
USB ESD protection
USB Client Circuit
VIN_USB Provides power to the OSD335x
24MHz RTC XO
See Connectors Sheet
JTAG connector
1M if populated
TODO add optional resistors from AM335X datasheet?
USB Host Circuit NOTE: if VIN_BAT is used, this will likely be below 5V as this input will come the battery circuit
XTALIN
VBUS goes to VIN_USB on OSD3358
1.1
USB camera connector
VSS_OSC
taken verbatim from PB,
